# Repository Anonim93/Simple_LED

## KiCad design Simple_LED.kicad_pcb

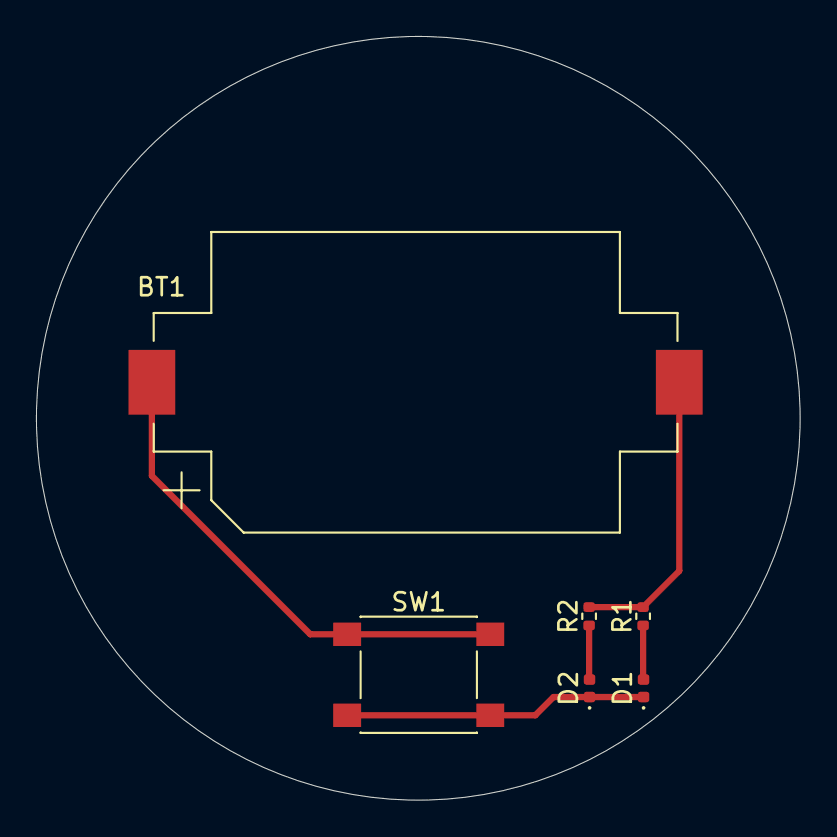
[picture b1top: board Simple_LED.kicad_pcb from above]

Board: 2 copper layers, 42.4 x 42.4 mm, 6 parts (0 on the bottom side), 5 nets.

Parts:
BT1: Battery_Cell; BatteryHolder_Keystone_1060_1x2032
D1, D2: LED; LED_0402_1005Metric
R1, R2: R_Small_US; R_0402_1005Metric
SW1: SW_Push_Dual_x2; SW_Push_1P1T_NO_6x6mm_H9.5mm

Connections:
unnamed: BT1.1 (+), SW1.1 (C)
unnamed: BT1.2 (-), R1.2, R2.2
unnamed: D1.2 (A), R1.1
unnamed: D1.1 (K), D2.1 (K), SW1.2 (D)
unnamed: D2.2 (A), R2.1

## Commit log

2024-04-21 Resistor & LED added to circuit
2024-04-21 Switch added to schematic
2024-04-21 Battery added to schematic
2024-04-21 2nd LED and resistor added
2024-04-22 created SMD PCB
2024-04-23 Created gerber file for Simple_LED_SMD
2024-04-23 added soundskrit_skr04xx symbol and footprint
2024-04-28 added .gitignore file
2024-04-28 updated .gitignore file to exlude backup folders
2024-04-28 updated .gitignore file
